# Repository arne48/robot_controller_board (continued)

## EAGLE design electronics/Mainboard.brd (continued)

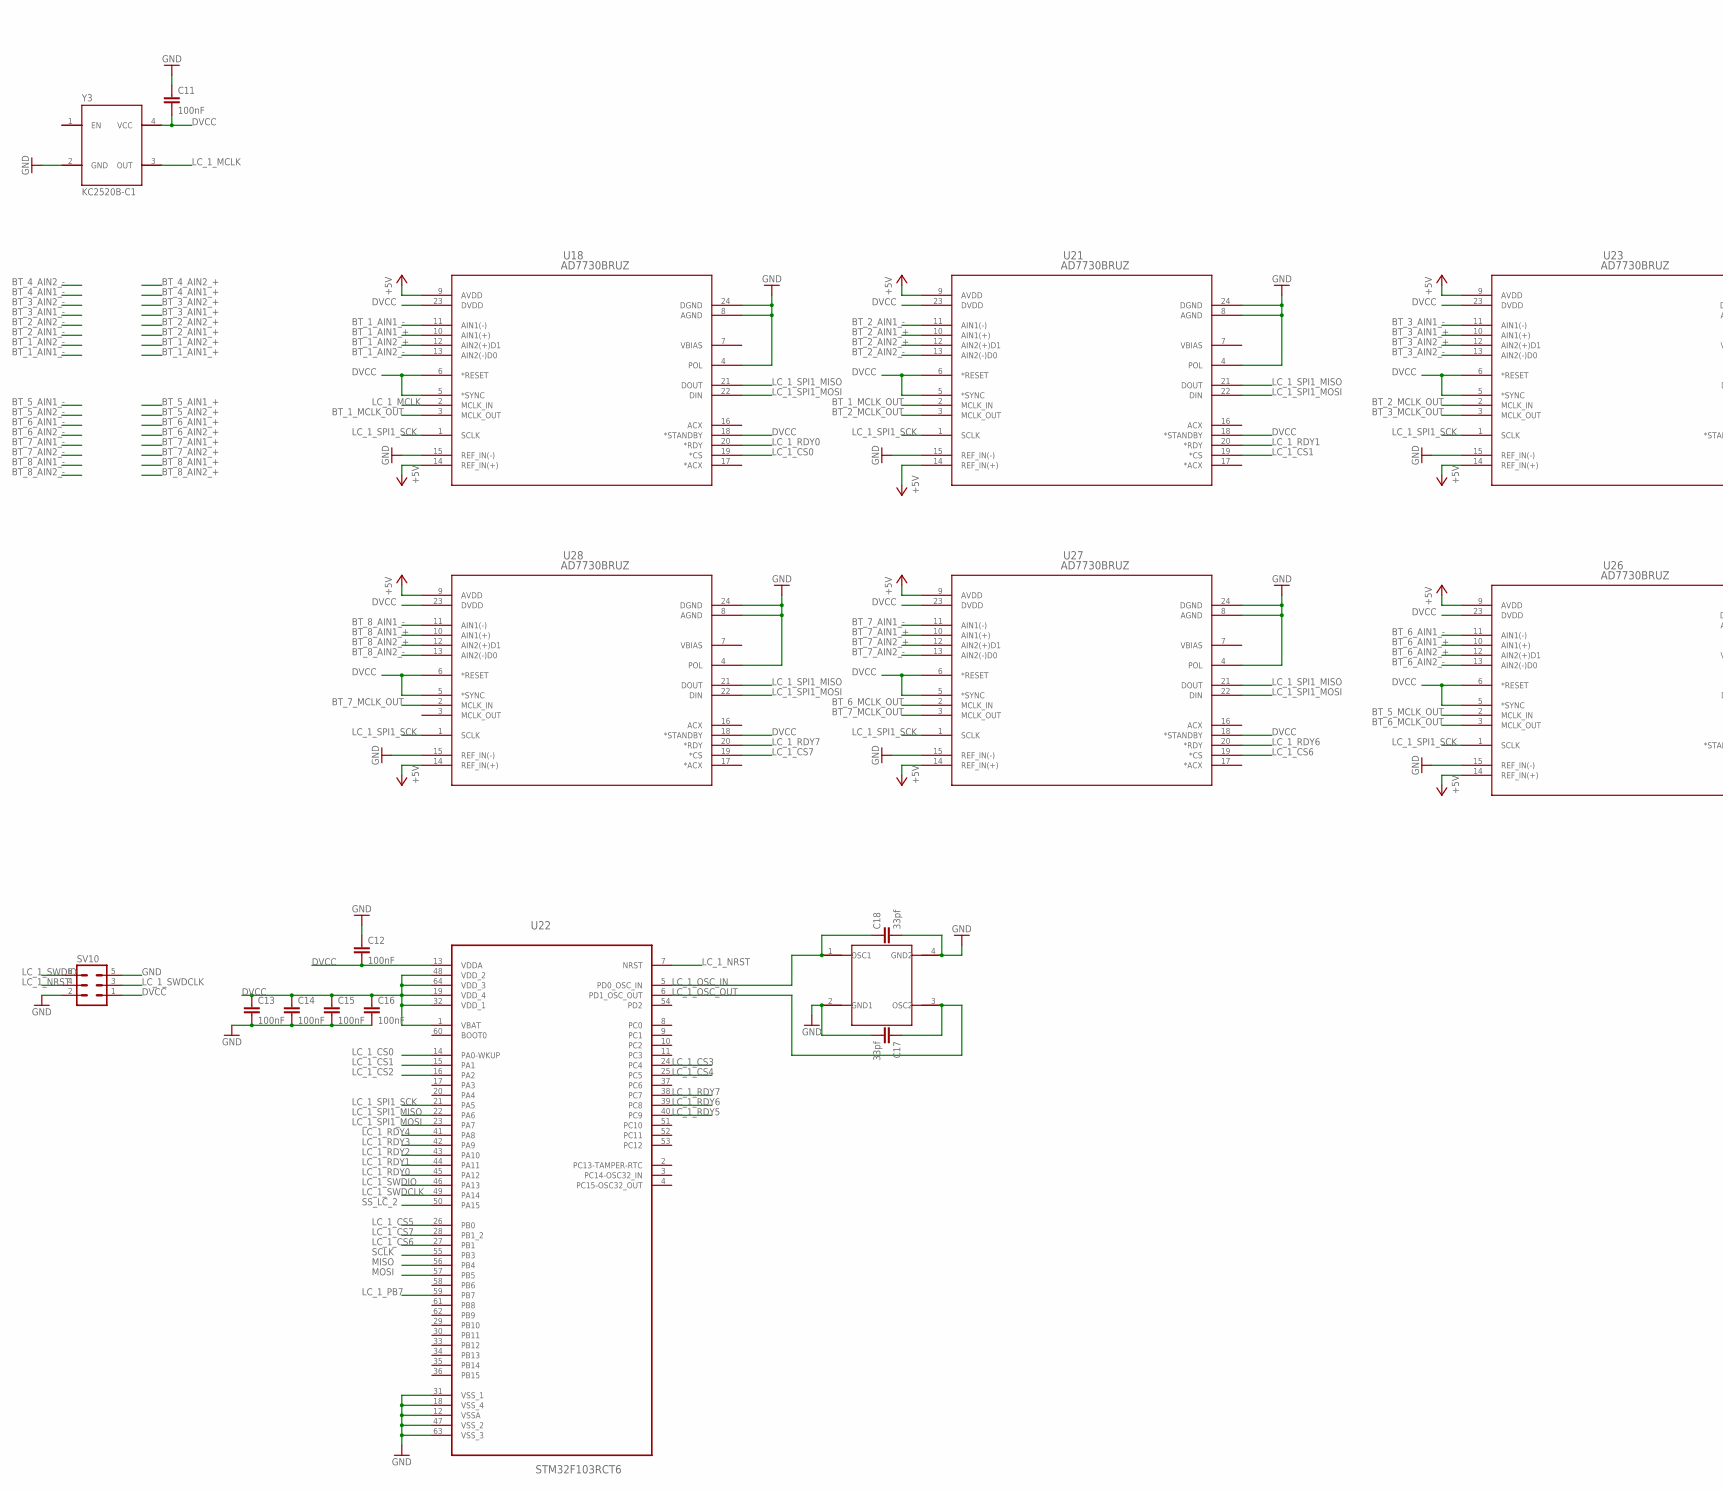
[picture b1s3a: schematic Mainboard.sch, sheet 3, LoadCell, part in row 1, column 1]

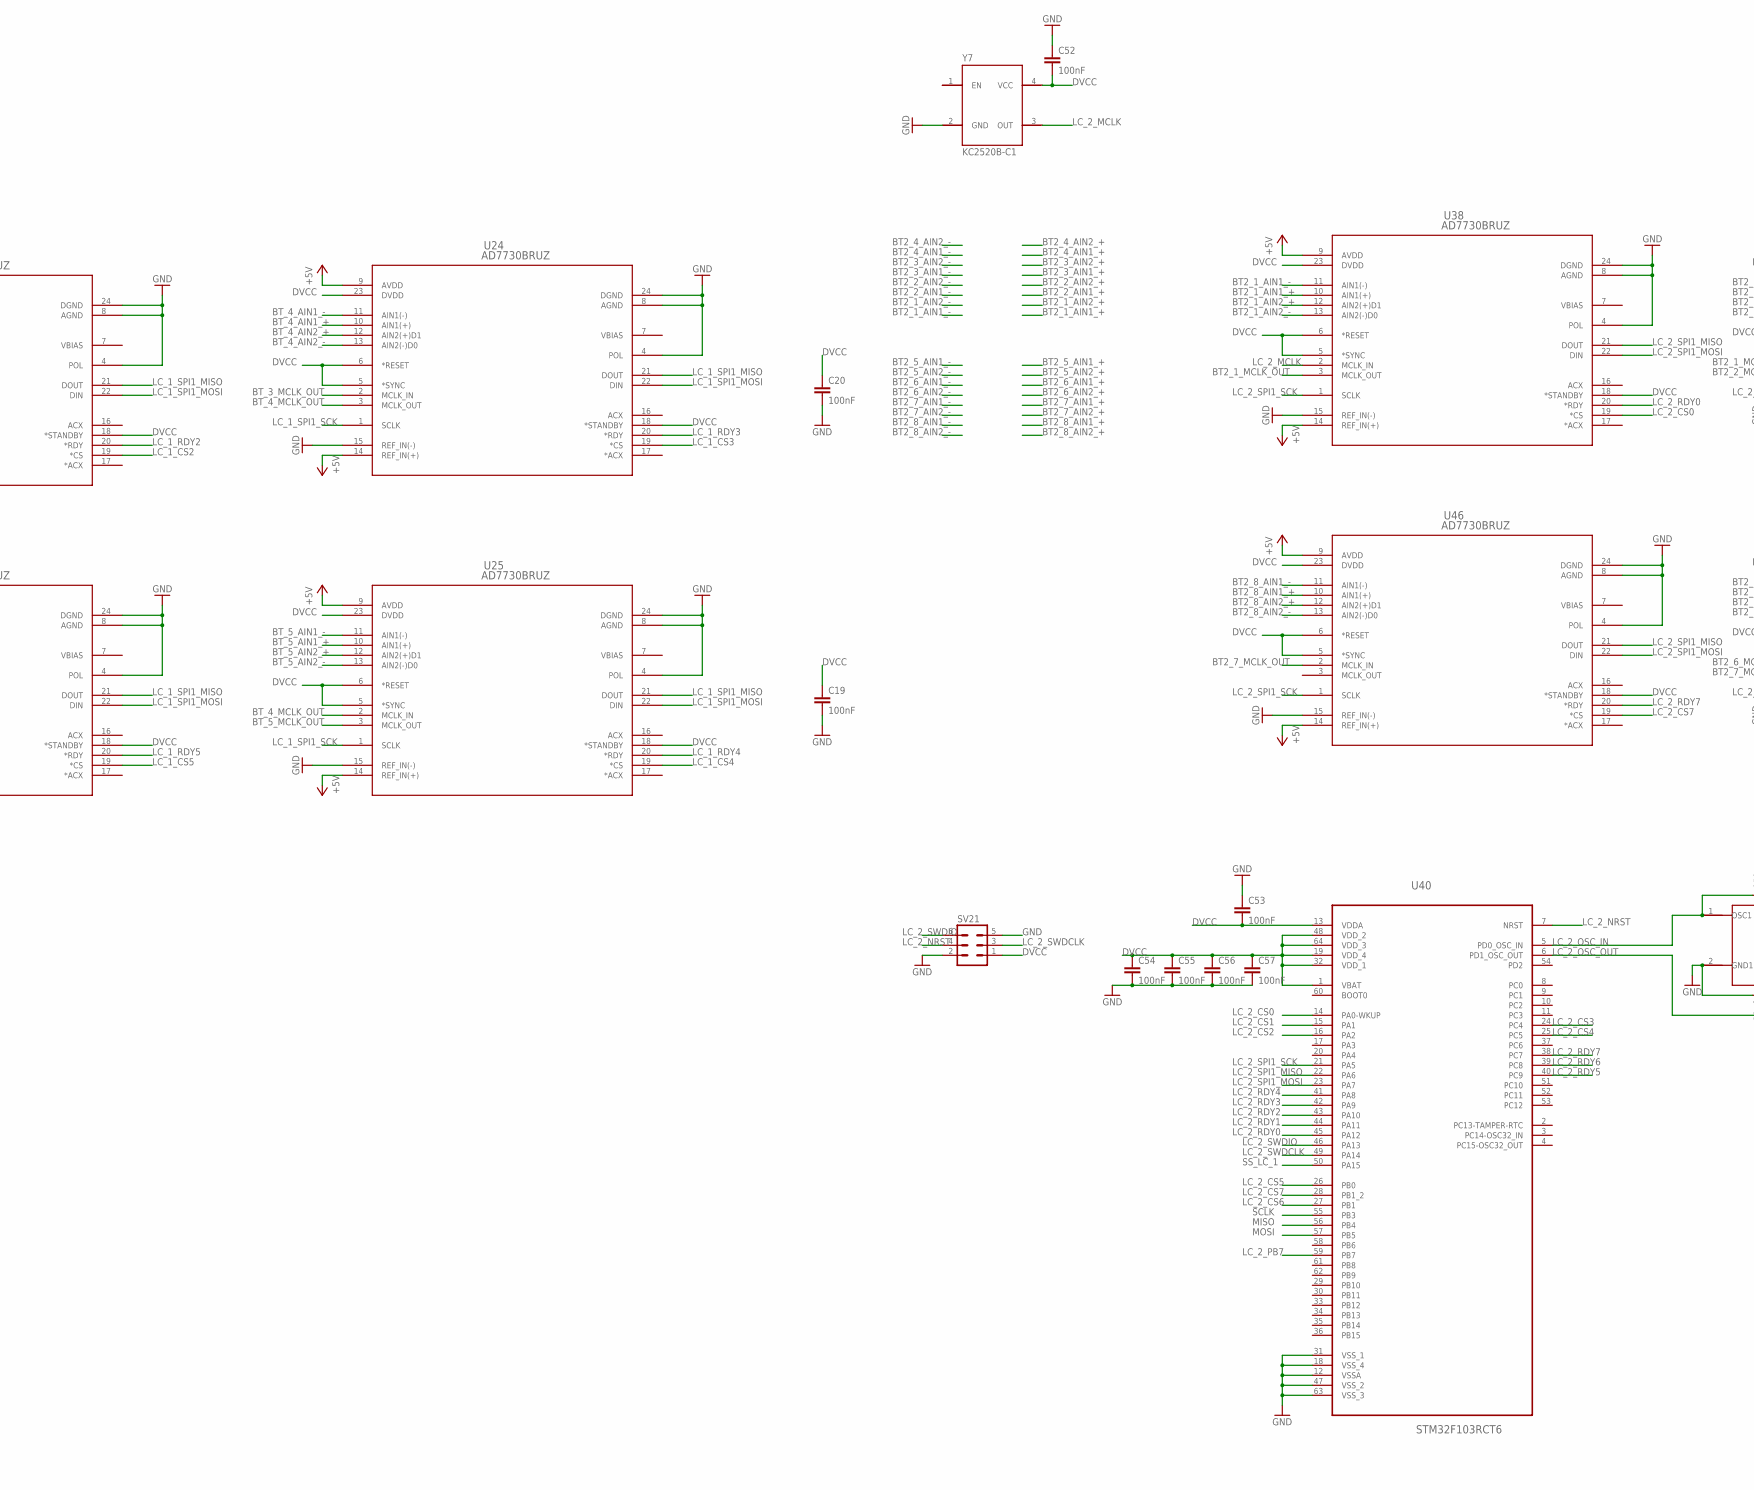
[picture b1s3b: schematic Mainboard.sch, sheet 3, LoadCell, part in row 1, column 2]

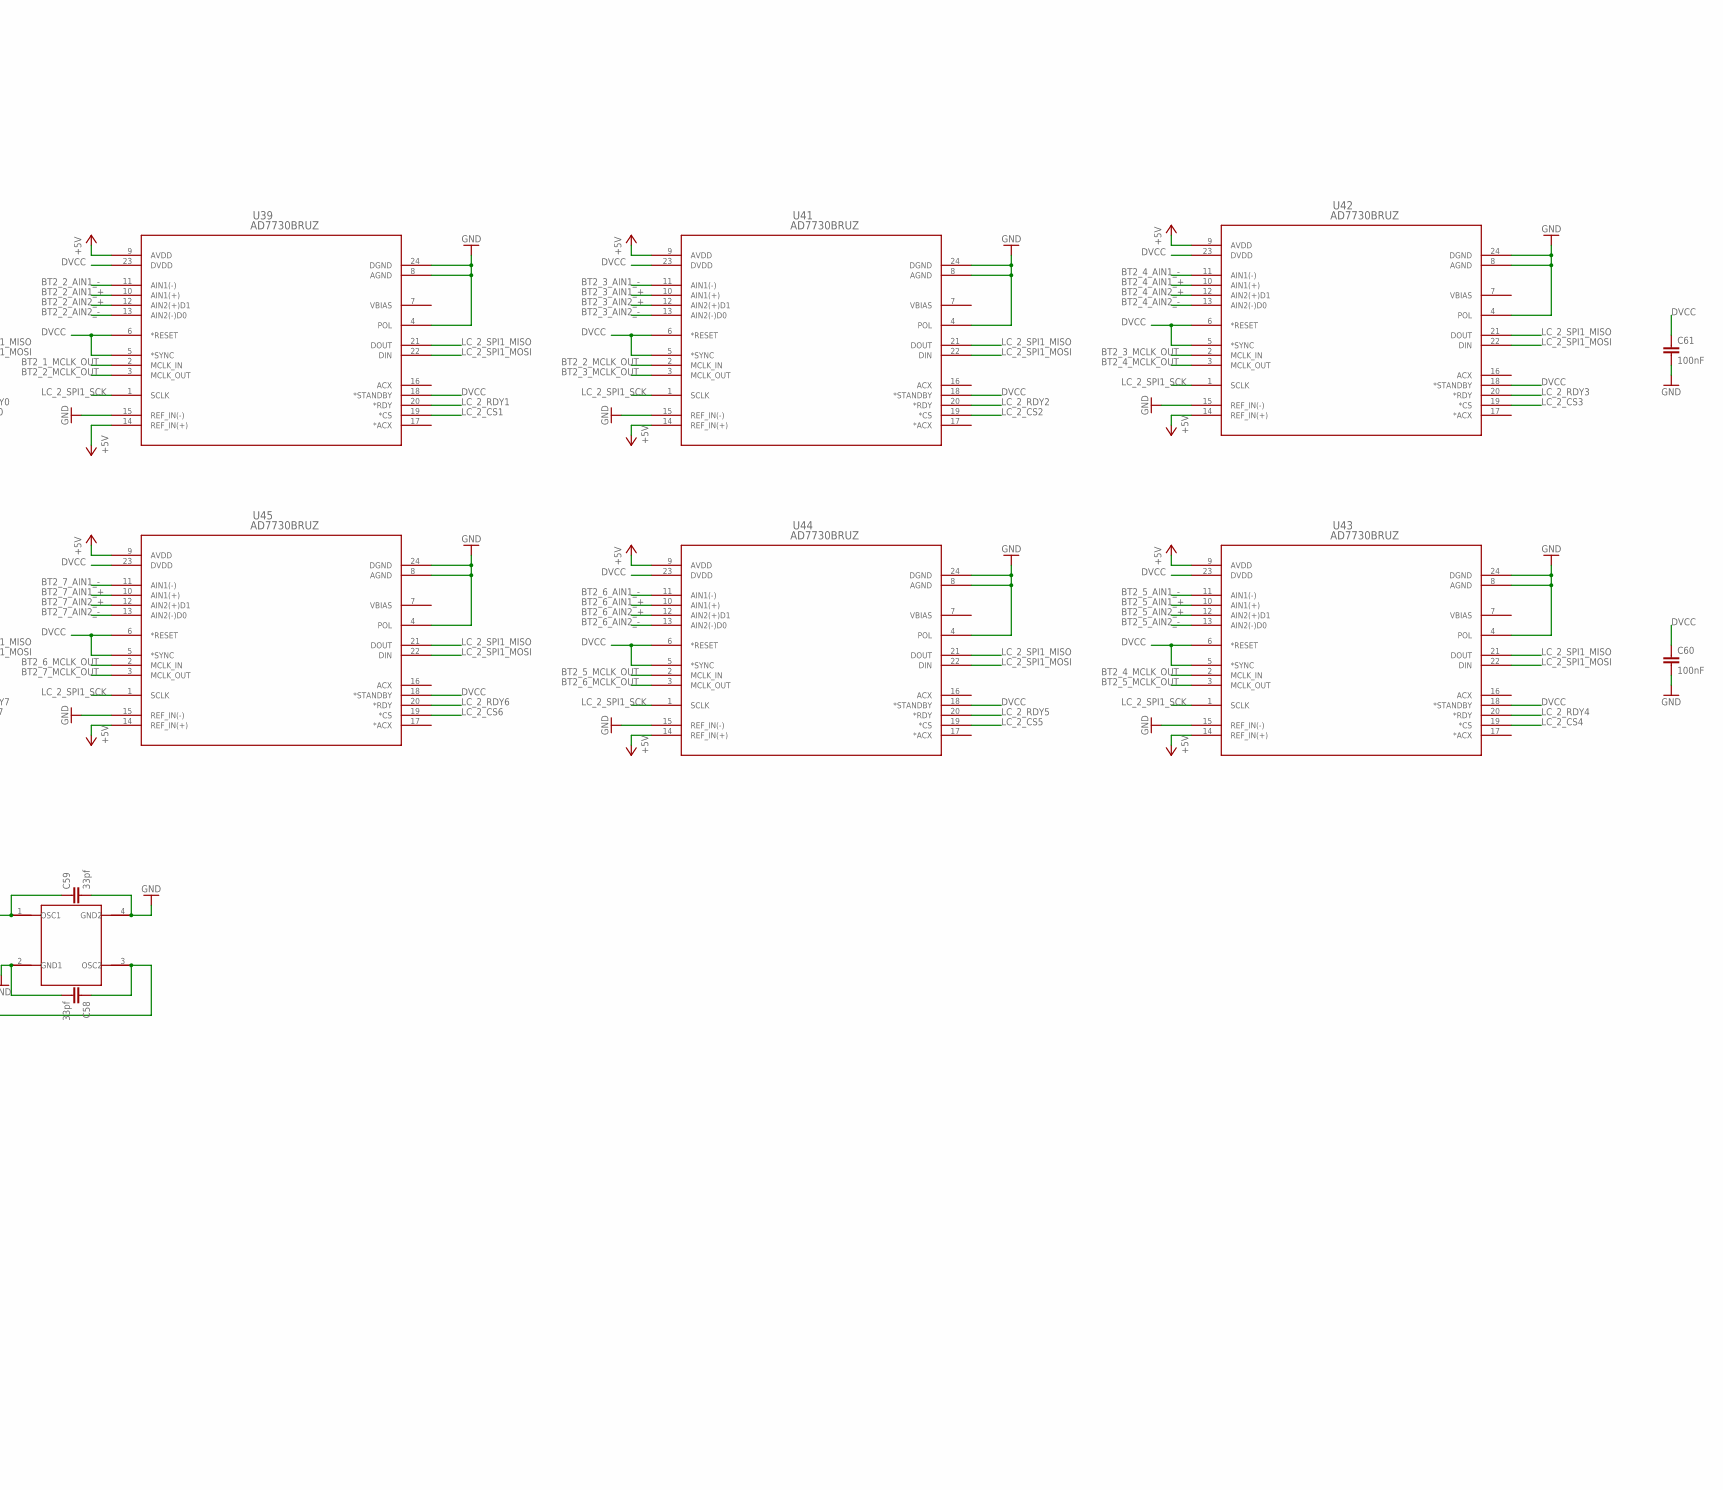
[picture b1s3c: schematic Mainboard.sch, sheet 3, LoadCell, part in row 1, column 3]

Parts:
C11, C12, C13, C14, C15, C16, C19, C20, C52, C53, C54, C55, C56, C57, C60, C61: 100nF; C0603
C17, C18, C58, C59: 33pf; C0603
SV10, SV21: MA03-2
U18, U21, U23, U24, U25, U26, U27, U28, U38, U39, U41, U42, U43, U44, U45, U46: AD7730BRUZ; RU_24
U22, U40: STM32F103RCT6; QFP50P1200X1200X160-64N
Y3, Y7: KC2520B-C1
Y4, Y8: ABM3B

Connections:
+5V: U18.9 (AVDD), U18.14 (REF_IN(+)), U21.9 (AVDD), U21.14 (REF_IN(+)), U23.9 (AVDD), U23.14 (REF_IN(+)), U24.9 (AVDD), U24.14 (REF_IN(+)), U25.9 (AVDD), U25.14 (REF_IN(+)), U26.9 (AVDD), U26.14 (REF_IN(+)), U27.9 (AVDD), U27.14 (REF_IN(+)), U28.9 (AVDD), U28.14 (REF_IN(+)), U38.9 (AVDD), U38.14 (REF_IN(+)), U39.9 (AVDD), U39.14 (REF_IN(+)), U41.9 (AVDD), U41.14 (REF_IN(+)), U42.9 (AVDD), U42.14 (REF_IN(+)), U43.9 (AVDD), U43.14 (REF_IN(+)), U44.9 (AVDD), U44.14 (REF_IN(+)), U45.9 (AVDD), U45.14 (REF_IN(+)), U46.9 (AVDD), U46.14 (REF_IN(+)); also elsewhere on the board
BT2_1_AIN1_+: U38.10 (AIN1(+)); also elsewhere on the board
BT2_1_AIN1_-: U38.11 (AIN1(-)); also elsewhere on the board
BT2_1_AIN2_+: U38.12 (AIN2(+)D1); also elsewhere on the board
BT2_1_AIN2_-: U38.13 (AIN2(-)D0); also elsewhere on the board
BT2_1_MCLK_OUT: U38.3 (MCLK_OUT), U39.2 (MCLK_IN)
BT2_2_AIN1_+: U39.10 (AIN1(+)); also elsewhere on the board
BT2_2_AIN1_-: U39.11 (AIN1(-)); also elsewhere on the board
BT2_2_AIN2_+: U39.12 (AIN2(+)D1); also elsewhere on the board
BT2_2_AIN2_-: U39.13 (AIN2(-)D0); also elsewhere on the board
BT2_2_MCLK_OUT: U39.3 (MCLK_OUT), U41.2 (MCLK_IN)
BT2_3_AIN1_+: U41.10 (AIN1(+)); also elsewhere on the board
BT2_3_AIN1_-: U41.11 (AIN1(-)); also elsewhere on the board
BT2_3_AIN2_+: U41.12 (AIN2(+)D1); also elsewhere on the board
BT2_3_AIN2_-: U41.13 (AIN2(-)D0); also elsewhere on the board
BT2_3_MCLK_OUT: U41.3 (MCLK_OUT), U42.2 (MCLK_IN)
BT2_4_AIN1_+: U42.10 (AIN1(+)); also elsewhere on the board
BT2_4_AIN1_-: U42.11 (AIN1(-)); also elsewhere on the board
BT2_4_AIN2_+: U42.12 (AIN2(+)D1); also elsewhere on the board
BT2_4_AIN2_-: U42.13 (AIN2(-)D0); also elsewhere on the board
BT2_4_MCLK_OUT: U42.3 (MCLK_OUT), U43.2 (MCLK_IN)
BT2_5_AIN1_+: U43.10 (AIN1(+)); also elsewhere on the board
BT2_5_AIN1_-: U43.11 (AIN1(-)); also elsewhere on the board
BT2_5_AIN2_+: U43.12 (AIN2(+)D1); also elsewhere on the board
BT2_5_AIN2_-: U43.13 (AIN2(-)D0); also elsewhere on the board
BT2_5_MCLK_OUT: U43.3 (MCLK_OUT), U44.2 (MCLK_IN)
BT2_6_AIN1_+: U44.10 (AIN1(+)); also elsewhere on the board
BT2_6_AIN1_-: U44.11 (AIN1(-)); also elsewhere on the board
BT2_6_AIN2_+: U44.12 (AIN2(+)D1); also elsewhere on the board
BT2_6_AIN2_-: U44.13 (AIN2(-)D0); also elsewhere on the board
BT2_6_MCLK_OUT: U44.3 (MCLK_OUT), U45.2 (MCLK_IN)
BT2_7_AIN1_+: U45.10 (AIN1(+)); also elsewhere on the board
BT2_7_AIN1_-: U45.11 (AIN1(-)); also elsewhere on the board
BT2_7_AIN2_+: U45.12 (AIN2(+)D1); also elsewhere on the board
BT2_7_AIN2_-: U45.13 (AIN2(-)D0); also elsewhere on the board
BT2_7_MCLK_OUT: U45.3 (MCLK_OUT), U46.2 (MCLK_IN)
BT2_8_AIN1_+: U46.10 (AIN1(+)); also elsewhere on the board
BT2_8_AIN1_-: U46.11 (AIN1(-)); also elsewhere on the board
BT2_8_AIN2_+: U46.12 (AIN2(+)D1); also elsewhere on the board
BT2_8_AIN2_-: U46.13 (AIN2(-)D0); also elsewhere on the board
BT_1_AIN1_+: U18.10 (AIN1(+)); also elsewhere on the board
BT_1_AIN1_-: U18.11 (AIN1(-)); also elsewhere on the board
BT_1_AIN2_+: U18.12 (AIN2(+)D1); also elsewhere on the board
BT_1_AIN2_-: U18.13 (AIN2(-)D0); also elsewhere on the board
BT_1_MCLK_OUT: U18.3 (MCLK_OUT), U21.2 (MCLK_IN)
BT_2_AIN1_+: U21.10 (AIN1(+)); also elsewhere on the board
BT_2_AIN1_-: U21.11 (AIN1(-)); also elsewhere on the board
BT_2_AIN2_+: U21.12 (AIN2(+)D1); also elsewhere on the board
BT_2_AIN2_-: U21.13 (AIN2(-)D0); also elsewhere on the board
BT_2_MCLK_OUT: U21.3 (MCLK_OUT), U23.2 (MCLK_IN)
BT_3_AIN1_+: U23.10 (AIN1(+)); also elsewhere on the board
BT_3_AIN1_-: U23.11 (AIN1(-)); also elsewhere on the board
BT_3_AIN2_+: U23.12 (AIN2(+)D1); also elsewhere on the board
BT_3_AIN2_-: U23.13 (AIN2(-)D0); also elsewhere on the board
BT_3_MCLK_OUT: U23.3 (MCLK_OUT), U24.2 (MCLK_IN)
BT_4_AIN1_+: U24.10 (AIN1(+)); also elsewhere on the board
BT_4_AIN1_-: U24.11 (AIN1(-)); also elsewhere on the board
BT_4_AIN2_+: U24.12 (AIN2(+)D1); also elsewhere on the board
BT_4_AIN2_-: U24.13 (AIN2(-)D0); also elsewhere on the board
BT_4_MCLK_OUT: U24.3 (MCLK_OUT), U25.2 (MCLK_IN)
BT_5_AIN1_+: U25.10 (AIN1(+)); also elsewhere on the board
BT_5_AIN1_-: U25.11 (AIN1(-)); also elsewhere on the board
BT_5_AIN2_+: U25.12 (AIN2(+)D1); also elsewhere on the board
BT_5_AIN2_-: U25.13 (AIN2(-)D0); also elsewhere on the board
BT_5_MCLK_OUT: U25.3 (MCLK_OUT), U26.2 (MCLK_IN)
BT_6_AIN1_+: U26.10 (AIN1(+)); also elsewhere on the board
BT_6_AIN1_-: U26.11 (AIN1(-)); also elsewhere on the board
BT_6_AIN2_+: U26.12 (AIN2(+)D1); also elsewhere on the board
BT_6_AIN2_-: U26.13 (AIN2(-)D0); also elsewhere on the board
BT_6_MCLK_OUT: U26.3 (MCLK_OUT), U27.2 (MCLK_IN)
BT_7_AIN1_+: U27.10 (AIN1(+)); also elsewhere on the board
BT_7_AIN1_-: U27.11 (AIN1(-)); also elsewhere on the board
BT_7_AIN2_+: U27.12 (AIN2(+)D1); also elsewhere on the board
BT_7_AIN2_-: U27.13 (AIN2(-)D0); also elsewhere on the board
BT_7_MCLK_OUT: U27.3 (MCLK_OUT), U28.2 (MCLK_IN)
BT_8_AIN1_+: U28.10 (AIN1(+)); also elsewhere on the board
BT_8_AIN1_-: U28.11 (AIN1(-)); also elsewhere on the board
BT_8_AIN2_+: U28.12 (AIN2(+)D1); also elsewhere on the board
BT_8_AIN2_-: U28.13 (AIN2(-)D0); also elsewhere on the board
DVCC: C11.2, C12.2, C13.1, C14.1, C15.1, C16.1, C19.1, C20.1, C52.2, C53.2, C54.1, C55.1, C56.1, C57.1, C60.1, C61.1, SV10.1, SV21.1, U18.5 (*SYNC), U18.6 (*RESET), U18.18 (*STANDBY), U18.23 (DVDD), U21.5 (*SYNC), U21.6 (*RESET), U21.18 (*STANDBY), U21.23 (DVDD), U22.1 (VBAT), U22.13 (VDDA), U22.19 (VDD_4), U22.32 (VDD_1), U22.48 (VDD_2), U22.64 (VDD_3), U23.5 (*SYNC), U23.6 (*RESET), U23.18 (*STANDBY), U23.23 (DVDD), U24.5 (*SYNC), U24.6 (*RESET), U24.18 (*STANDBY), U24.23 (DVDD), U25.5 (*SYNC), U25.6 (*RESET), U25.18 (*STANDBY), U25.23 (DVDD), U26.5 (*SYNC), U26.6 (*RESET), U26.18 (*STANDBY), U26.23 (DVDD), U27.5 (*SYNC), U27.6 (*RESET), U27.18 (*STANDBY), U27.23 (DVDD), U28.5 (*SYNC), U28.6 (*RESET), U28.18 (*STANDBY), U28.23 (DVDD), U38.5 (*SYNC), U38.6 (*RESET), U38.18 (*STANDBY), U38.23 (DVDD), U39.5 (*SYNC), U39.6 (*RESET), U39.18 (*STANDBY), U39.23 (DVDD), U40.1 (VBAT), U40.13 (VDDA), U40.19 (VDD_4), U40.32 (VDD_1), U40.48 (VDD_2), U40.64 (VDD_3), U41.5 (*SYNC), U41.6 (*RESET), U41.18 (*STANDBY), U41.23 (DVDD), U42.5 (*SYNC), U42.6 (*RESET), U42.18 (*STANDBY), U42.23 (DVDD), U43.5 (*SYNC), U43.6 (*RESET), U43.18 (*STANDBY), U43.23 (DVDD), U44.5 (*SYNC), U44.6 (*RESET), U44.18 (*STANDBY), U44.23 (DVDD), U45.5 (*SYNC), U45.6 (*RESET), U45.18 (*STANDBY), U45.23 (DVDD), U46.5 (*SYNC), U46.6 (*RESET), U46.18 (*STANDBY), U46.23 (DVDD), Y3.4 (VCC), Y7.4 (VCC); also elsewhere on the board
GND: C11.1, C12.1, C13.2, C14.2, C15.2, C16.2, C17.2, C18.2, C19.2, C20.2, C52.1, C53.1, C54.2, C55.2, C56.2, C57.2, C58.2, C59.2, C60.2, C61.2, SV10.2, SV10.5, SV21.2, SV21.5, U18.4 (POL), U18.8 (AGND), U18.15 (REF_IN(-)), U18.24 (DGND), U21.4 (POL), U21.8 (AGND), U21.15 (REF_IN(-)), U21.24 (DGND), U22.12 (VSSA), U22.18 (VSS_4), U22.31 (VSS_1), U22.47 (VSS_2), U22.63 (VSS_3), U23.4 (POL), U23.8 (AGND), U23.15 (REF_IN(-)), U23.24 (DGND), U24.4 (POL), U24.8 (AGND), U24.15 (REF_IN(-)), U24.24 (DGND), U25.4 (POL), U25.8 (AGND), U25.15 (REF_IN(-)), U25.24 (DGND), U26.4 (POL), U26.8 (AGND), U26.15 (REF_IN(-)), U26.24 (DGND), U27.4 (POL), U27.8 (AGND), U27.15 (REF_IN(-)), U27.24 (DGND), U28.4 (POL), U28.8 (AGND), U28.15 (REF_IN(-)), U28.24 (DGND), U38.4 (POL), U38.8 (AGND), U38.15 (REF_IN(-)), U38.24 (DGND), U39.4 (POL), U39.8 (AGND), U39.15 (REF_IN(-)), U39.24 (DGND), U40.12 (VSSA), U40.18 (VSS_4), U40.31 (VSS_1), U40.47 (VSS_2), U40.63 (VSS_3), U41.4 (POL), U41.8 (AGND), U41.15 (REF_IN(-)), U41.24 (DGND), U42.4 (POL), U42.8 (AGND), U42.15 (REF_IN(-)), U42.24 (DGND), U43.4 (POL), U43.8 (AGND), U43.15 (REF_IN(-)), U43.24 (DGND), U44.4 (POL), U44.8 (AGND), U44.15 (REF_IN(-)), U44.24 (DGND), U45.4 (POL), U45.8 (AGND), U45.15 (REF_IN(-)), U45.24 (DGND), U46.4 (POL), U46.8 (AGND), U46.15 (REF_IN(-)), U46.24 (DGND), Y3.2 (GND), Y4.2 (GND1), Y4.4 (GND2), Y7.2 (GND), Y8.2 (GND1), Y8.4 (GND2); also elsewhere on the board
LC_1_CS0: U18.19 (*CS), U22.14 (PA0-WKUP)
LC_1_CS1: U21.19 (*CS), U22.15 (PA1)
LC_1_CS2: U22.16 (PA2), U23.19 (*CS)
LC_1_CS3: U22.24 (PC4), U24.19 (*CS)
LC_1_CS4: U22.25 (PC5), U25.19 (*CS)
LC_1_CS5: U22.26 (PB0), U26.19 (*CS)
LC_1_CS6: U22.27 (PB1), U27.19 (*CS)
LC_1_CS7: U22.28 (PB1_2), U28.19 (*CS)
LC_1_MCLK: U18.2 (MCLK_IN), Y3.3 (OUT)
LC_1_NRST: SV10.4, U22.7 (NRST)
LC_1_OSC_IN: C18.1, U22.5 (PD0_OSC_IN), Y4.1 (OSC1)
LC_1_OSC_OUT: C17.1, U22.6 (PD1_OSC_OUT), Y4.3 (OSC2)
LC_1_PB7: U22.59 (PB7)
LC_1_RDY0: U18.20 (*RDY), U22.45 (PA12)
LC_1_RDY1: U21.20 (*RDY), U22.44 (PA11)
LC_1_RDY2: U22.43 (PA10), U23.20 (*RDY)
LC_1_RDY3: U22.42 (PA9), U24.20 (*RDY)
LC_1_RDY4: U22.41 (PA8), U25.20 (*RDY)
LC_1_RDY5: U22.40 (PC9), U26.20 (*RDY)
LC_1_RDY6: U22.39 (PC8), U27.20 (*RDY)
LC_1_RDY7: U22.38 (PC7), U28.20 (*RDY)
LC_1_SPI1_MISO: U18.21 (DOUT), U21.21 (DOUT), U22.22 (PA6), U23.21 (DOUT), U24.21 (DOUT), U25.21 (DOUT), U26.21 (DOUT), U27.21 (DOUT), U28.21 (DOUT)
LC_1_SPI1_MOSI: U18.22 (DIN), U21.22 (DIN), U22.23 (PA7), U23.22 (DIN), U24.22 (DIN), U25.22 (DIN), U26.22 (DIN), U27.22 (DIN), U28.22 (DIN)
LC_1_SPI1_SCK: U18.1 (SCLK), U21.1 (SCLK), U22.21 (PA5), U23.1 (SCLK), U24.1 (SCLK), U25.1 (SCLK), U26.1 (SCLK), U27.1 (SCLK), U28.1 (SCLK)
LC_1_SWDCLK: SV10.3, U22.49 (PA14)
LC_1_SWDIO: SV10.6, U22.46 (PA13)
LC_2_CS0: U38.19 (*CS), U40.14 (PA0-WKUP)
LC_2_CS1: U39.19 (*CS), U40.15 (PA1)
LC_2_CS2: U40.16 (PA2), U41.19 (*CS)
LC_2_CS3: U40.24 (PC4), U42.19 (*CS)
LC_2_CS4: U40.25 (PC5), U43.19 (*CS)
LC_2_CS5: U40.26 (PB0), U44.19 (*CS)
LC_2_CS6: U40.27 (PB1), U45.19 (*CS)
LC_2_CS7: U40.28 (PB1_2), U46.19 (*CS)
LC_2_MCLK: U38.2 (MCLK_IN), Y7.3 (OUT)
LC_2_NRST: SV21.4, U40.7 (NRST)
LC_2_OSC_IN: C59.1, U40.5 (PD0_OSC_IN), Y8.1 (OSC1)
LC_2_OSC_OUT: C58.1, U40.6 (PD1_OSC_OUT), Y8.3 (OSC2)
LC_2_PB7: U40.59 (PB7)
LC_2_RDY0: U38.20 (*RDY), U40.45 (PA12)
LC_2_RDY1: U39.20 (*RDY), U40.44 (PA11)
LC_2_RDY2: U40.43 (PA10), U41.20 (*RDY)
LC_2_RDY3: U40.42 (PA9), U42.20 (*RDY)
LC_2_RDY4: U40.41 (PA8), U43.20 (*RDY)
LC_2_RDY5: U40.40 (PC9), U44.20 (*RDY)
LC_2_RDY6: U40.39 (PC8), U45.20 (*RDY)
LC_2_RDY7: U40.38 (PC7), U46.20 (*RDY)
LC_2_SPI1_MISO: U38.21 (DOUT), U39.21 (DOUT), U40.22 (PA6), U41.21 (DOUT), U42.21 (DOUT), U43.21 (DOUT), U44.21 (DOUT), U45.21 (DOUT), U46.21 (DOUT)
LC_2_SPI1_MOSI: U38.22 (DIN), U39.22 (DIN), U40.23 (PA7), U41.22 (DIN), U42.22 (DIN), U43.22 (DIN), U44.22 (DIN), U45.22 (DIN), U46.22 (DIN)
LC_2_SPI1_SCK: U38.1 (SCLK), U39.1 (SCLK), U40.21 (PA5), U41.1 (SCLK), U42.1 (SCLK), U43.1 (SCLK), U44.1 (SCLK), U45.1 (SCLK), U46.1 (SCLK)
LC_2_SWDCLK: SV21.3, U40.49 (PA14)
LC_2_SWDIO: SV21.6, U40.46 (PA13)
MISO: U22.56 (PB4), U40.56 (PB4); also elsewhere on the board
MOSI: U22.57 (PB5), U40.57 (PB5); also elsewhere on the board
SCLK: U22.55 (PB3), U40.55 (PB3); also elsewhere on the board
SS_LC_1: U40.50 (PA15); also elsewhere on the board
SS_LC_2: U22.50 (PA15); also elsewhere on the board
